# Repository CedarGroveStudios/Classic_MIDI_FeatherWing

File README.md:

# Classic_MIDI_FeatherWing

### _A classic MIDI interface FeatherWing with provisions for DIN-5 and TRS TypeB connectors_

The Classic MIDI FeatherWing interface is an Adafruit Feather-compatible module. Deriving its power from the host Feather's 3.3V power, the interface converts incoming and outgoing classic MIDI current-loop input and output to Feather UART (RX and TX) logic pins.

The wing provides on-board input and output footprints for 3.5mm TRS Type B and DIN-5 connectors while maintaining the Feather dimensional format, thanks to John Park's inspirational _Feather MIDI Nub_ design (Twitter: @johnedgarpark). The MIDI input is an optically-isolated connection. MIDI output is buffered and current-limited. On-board receive (RX) and transmit (TX) LEDs indicate incoming and outgoing signals.

To use the wing as a standalone MIDI interface, see the UART-STEMMA MIDI Backpack project: https://github.com/CedarGroveStudios/UART-STEMMA_MIDI_Backpack

DIN-5 MIDI jack used: https://www.adafruit.com/product/1134

3.5mm TRS MIDI jack used: https://www.adafruit.com/product/1699

The Classic MIDI interface was tested with CircuitPython version 4.1.0 beta 1 and earlier releases. Example code is provided in the repository. Additional code examples can be found within the _adafruit__midi_ CircuitPython examples distribution.

OSH Park project: https://oshpark.com/shared_projects/SzjsJUV0

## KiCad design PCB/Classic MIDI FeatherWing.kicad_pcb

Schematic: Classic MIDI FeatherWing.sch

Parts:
C1: 0.1uF; C_0805_HandSoldering
C2: 10uF; C_0805_HandSoldering
D1: 1N4001; D_0805_hand_soldering
D2, D3: LED; LED_0805_HandSoldering
J1: MIDI_IN; CUI_SDS-50J
J2: MIDI_OUT; CUI_SDS-50J
J3: TRS_MIDI_IN; STX-3120-5_3.5mm
J4: TRS_MIDI_OUT; STX-3120-5_3.5mm
R1, R5, R6: 220; R_0805_HandSoldering
R2: 10K; R_0805_HandSoldering
R3, R4: 47; R_0805_HandSoldering
THRU1: Solder_Jumper_0805; 0805_Solder_Jumper
U1: ICPL0601; SOIC-8_3.9x4.9mm_Pitch1.27mm
U2, U3, U5: 74HCT1G125; TSOP-5_1.65x3.05mm_Pitch0.95mm_hand_solder
U4: Feather; Adafruit_Feather_M4_Express_bare

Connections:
+3V3: C1.1, C2.1, R2.1, R4.1, R5.2, R6.2, U1.8 (Vcc), U2.6, U3.6, U4.2, U5.6
/Rx: R2.2, THRU1.1, U1.6 (OC_OUT), U3.2, U4.14
/Tx: THRU1.2, U2.2, U4.15, U5.2
GND: C1.2, C2.2, J2.2, J4.1, U1.5 (GND), U2.1, U2.3, U3.1, U3.3, U4.4, U5.1, U5.3
unnamed: D1.1, R1.2, U1.2 (IN+)
unnamed: D1.2, J1.5, J3.2, U1.3 (IN-)
unnamed: D2.1, U5.4
unnamed: D2.2, R5.1
unnamed: D3.1, U3.4
unnamed: D3.2, R6.1
unnamed: J1.4, J3.5, R1.1
unnamed: J2.4, J4.5, R4.2
unnamed: J2.5, J4.2, R3.1
unnamed: R3.2, U2.4

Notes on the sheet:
SHIELD
POWER MGT
MODULE FOUNDATION
GRN Tx
RED Rx
bridge to enable MIDI THRU
TRS MIDI TYPE B

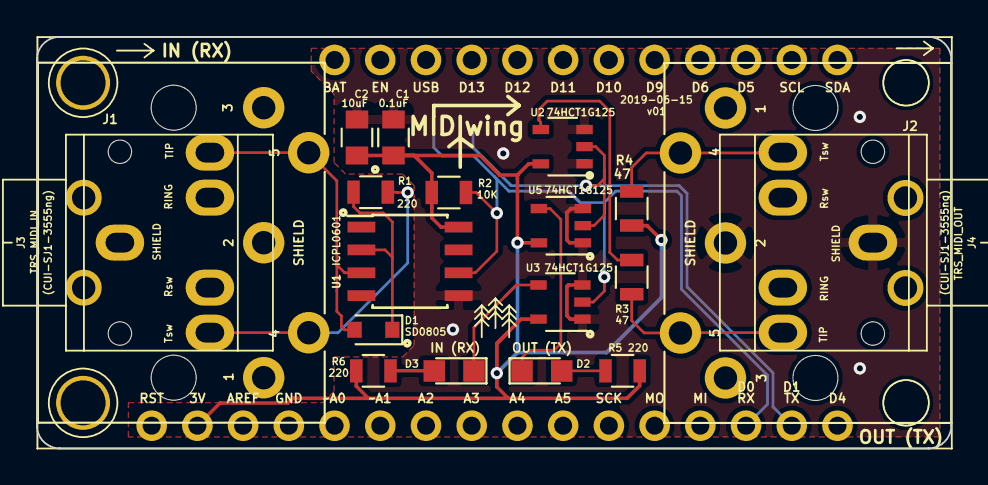
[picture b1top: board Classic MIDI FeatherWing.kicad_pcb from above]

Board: 2 copper layers, 50.8 x 22.9 mm, 21 parts (1 on the bottom side), 14 nets.

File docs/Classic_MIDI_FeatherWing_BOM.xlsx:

Reference | Value | Desc | Footprint | DigiKey
C1 | 0.1uF | capacitor | 0805
C2 | 10uF | capacitor | 0805
D1 | Diode | schottky 40v, 0.5A | 0805 | https://www.digikey.com/product-detail/en/avx-corporation/SD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
J1, J2 |  | DIN-5 jack | THT | https://www.adafruit.com/product/1134
J3, J4 |  | 3.5mm TRS Jack | THT | https://www.adafruit.com/product/1699
R1, R5, R6 | 220 ohm | resistor | 0805
R2 | 10K ohm | resistor | 0805
R3, R4 | 47 ohm | resistor | 0805
U1 | ICPL0601 | opto-isolator | SOIC-8 | https://www.digikey.com/products/en?keywords=icpl0601smct-nd
U2, U3, U5 | 74HCT1G125 | tri-state buffer | TSOP-5 | https://www.digikey.com/products/en?keywords=1727-6054-1-nd

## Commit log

2019-07-30 fix fast tempo error
2019-08-08 update repo structure
2019-08-11 update for PyGamer screen
2019-08-11 make BPM calculation and display optional
2019-08-11 add capability to select MIDI Thru and BPM calculation
2019-08-12 updated sniffer test video
2019-08-13 update schematic and add BOM spreadsheet
2019-08-13 update silkscreen
2019-08-13 update OSH Park shared link
2019-08-13 updated silk screen and OSH Park shared project link
2019-11-16 update photos
2021-07-12 update documentation
